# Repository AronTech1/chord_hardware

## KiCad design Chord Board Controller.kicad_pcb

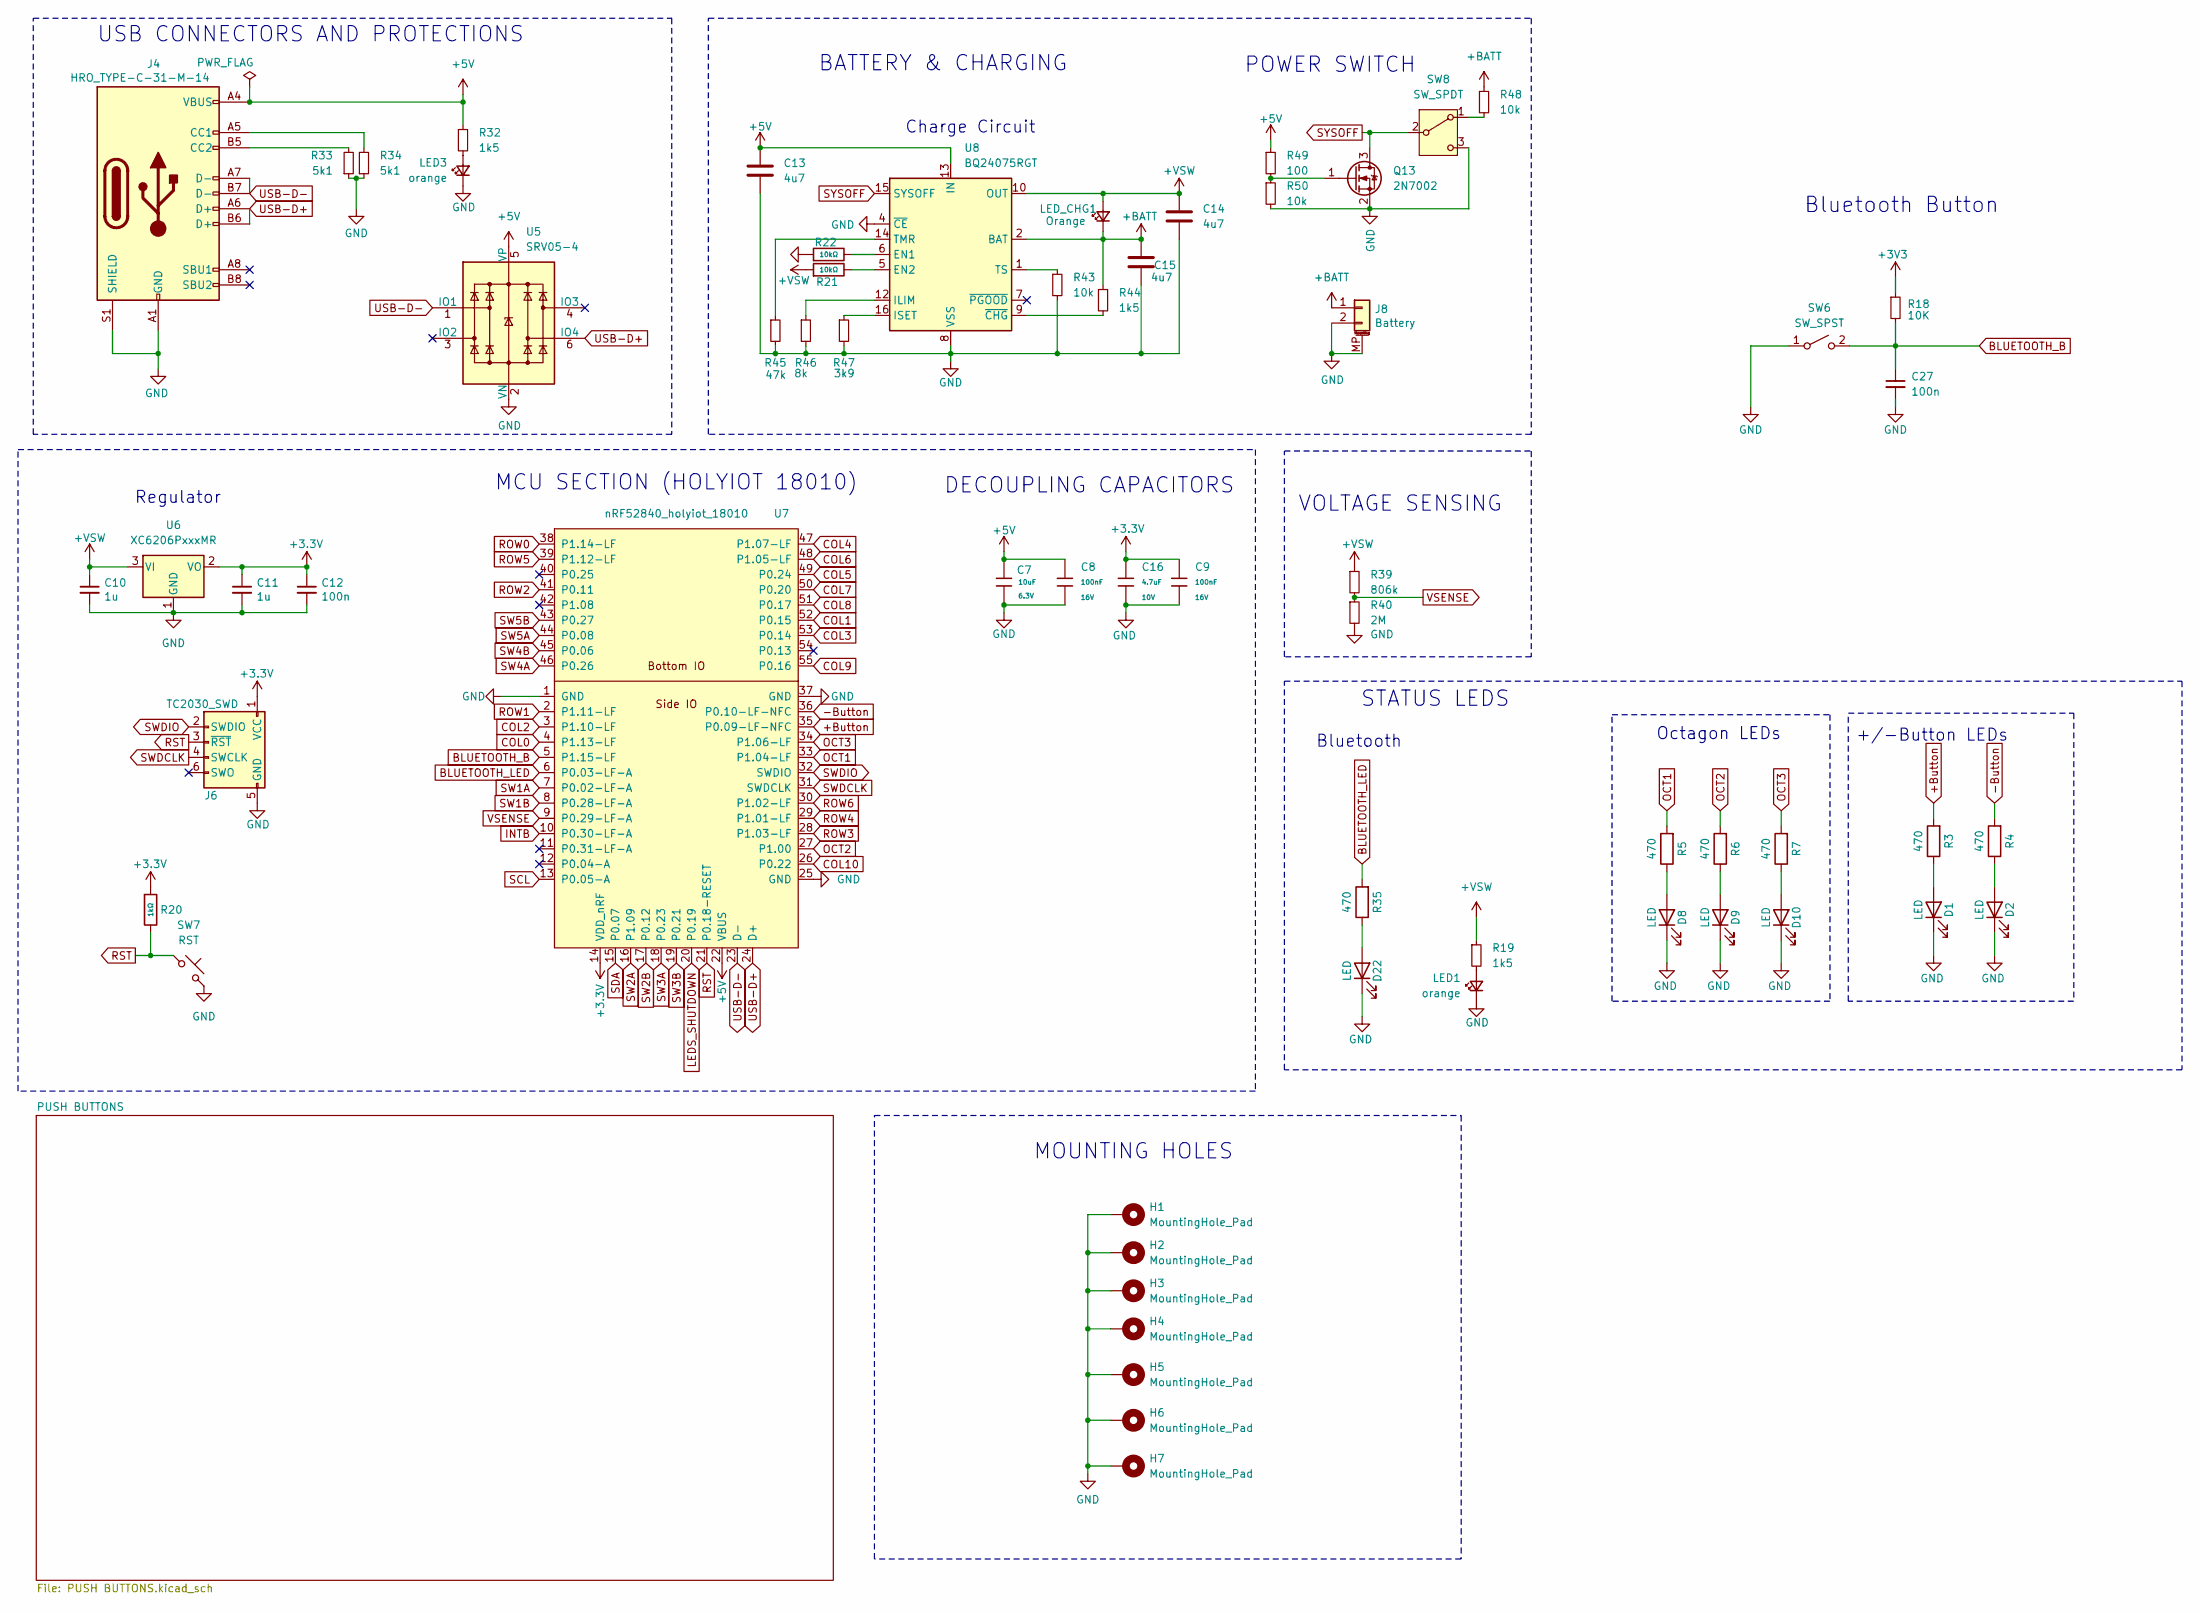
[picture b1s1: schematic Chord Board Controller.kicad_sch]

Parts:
C7: 10uF; C_0402; Voltage Rated 6.3V; Tolerance ±20%; Part CL05A106MQ5NUNC; LCSC C15525
C8, C9: 100nF; C_0402; Voltage Rated 16V; Tolerance ±10%; Part CL05B104KO5NNNC; LCSC C1525
C10, C11: 1u; C_0402_1005Metric; MFR.Part # CL05A105KP5NNNC; JLCPCB part# C14445
C12: 100n; C_0402_1005Metric; MFR.Part # CL05B104KO5NNNC; JLCPCB part# C1525
C13, C14, C15: 4u7; C_0603_1608Metric
C16: 4.7uF; C_0402; Voltage Rated 10V; Tolerance ±20%; Part CL05A475MP5NRNC; LCSC C23733
C27: 100n; C_0402_1005Metric_Pad0.74x0.62mm_HandSolder; Manufacturer Part # GCM155R71H104KE02J; LCSC C2649549
D1, D2, D8, D9, D10: LED; LED_0603_1608Metric
D22: LED; LED_D1.8mm_W1.8mm_H2.4mm_Horizontal_O6.35mm_Z8.2mm
H1, H2, H3, H4, H5, H6, H7: MountingHole_Pad; MountingHole_2.2mm_M2; MFR.Part # DNP; JLCPCB part# DNP
J4: HRO_TYPE-C-31-M-14; USB_C_Receptacle_HRO_TYPE-C-31-M-14; MFR.Part # TYPE-C-31-M-12; JLCPCB part# C165948
J6: TC2030_SWD; CON_TC2030_outlined; MFR.Part # DNP; JLCPCB part# DNP
J8: Battery; JST_PH_S2B-PH-K_1x02_P2.00mm_Horizontal; LCSC C505023
LED1, LED3: orange; LED_D1.8mm_W1.8mm_H2.4mm_Horizontal_O6.35mm_Z8.2mm
LED_CHG1: Orange; LED_D1.8mm_W1.8mm_H2.4mm_Horizontal_O6.35mm_Z8.2mm
Q13: 2N7002; SOT-23
R3, R4, R5, R6, R7: 470; R_0402_1005Metric
R18: 10K; R_0402_1005Metric_Pad0.72x0.64mm_HandSolder; Manufacturer Part # CRCW040210K0FKED; LCSC C71617
R19, R32: 1k5; R_0402_1005Metric; MFR.Part # 0402WGF1501TCE; JLCPCB part# C25867
R20: 1kΩ; R_0402; Overload Voltage (Max) 50V; Tolerance ±1%; Part 0402WGF1001TCE; LCSC C11702
R21, R22: 10kΩ; R_0402; Overload Voltage (Max) 50V; Tolerance ±1%; Part 0402WGF1002TCE; LCSC C25744
R33, R34: 5k1; R_0402_1005Metric; MFR.Part # 0402WGF5101TCE; JLCPCB part# C25905
R35: 470; R_0603
R39: 806k; R_0402_1005Metric; MFR.Part # 0402WGF8063TCE; JLCPCB part# C29263
R40: 2M; R_0402_1005Metric; MFR.Part # 0402WGF2004TCE; JLCPCB part# C11512
R43, R48, R50: 10k; R_0603_1608Metric_Pad0.98x0.95mm_HandSolder
R44: 1k5; R_0603_1608Metric_Pad0.98x0.95mm_HandSolder
R45: 47k; R_0603_1608Metric_Pad0.98x0.95mm_HandSolder
R46: 8k; R_0603_1608Metric_Pad0.98x0.95mm_HandSolder
R47: 3k9; R_0603_1608Metric_Pad0.98x0.95mm_HandSolder
R49: 100; R_0603_1608Metric_Pad0.98x0.95mm_HandSolder
SW6: SW_SPST; SW_Tactile_SPST_Angled_PTS645Vx31-2LFS; Manufacturer Part # DTSA-61K-V; LCSC C483771
SW7: RST; SW_SPST_SKQG_WithStem; MFR.Part # FRC0402F1101TS; JLCPCB part# C2909306
SW8: SW_SPDT; SW_MSK12C02-HB
U5: SRV05-4; SOT-23-6; MFR.Part # SRV05-4-P-T7; JLCPCB part# C179173
U6: XC6206PxxxMR; SOT-23; MFR.Part # XC6202P332MR-G; JLCPCB part# C47374
U7: nRF52840_holyiot_18010
U8: BQ24075RGT; VQFN-16-1EP_3x3mm_P0.5mm_EP1.6x1.6mm

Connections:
+3.3V: C9.1, C11.1, C12.1, C16.1, J6.1 (VCC), R20.1, U6.2 (VO), U7.14 (VDD_nRF)
+3V3: R18.1
+BATT: C15.1, J8.1, LED_CHG1.1 (K), R44.1, R48.1, U8.2 (BAT), U8.3 (BAT)
+Button: R3.2, U7.35 (P0.09-LF-NFC)
-Button: R4.2, U7.36 (P0.10-LF-NFC)
BLUETOOTH_B: C27.1, R18.2, SW6.2 (B), U7.5 (P1.15-LF)
BLUETOOTH_LED: R35.2, U7.6 (P0.03-LF-A)
COL0: U7.4 (P1.13-LF); also elsewhere on the board
COL1: U7.52 (P0.15); also elsewhere on the board
COL2: U7.3 (P1.10-LF); also elsewhere on the board
COL3: U7.53 (P0.14); also elsewhere on the board
COL4: U7.47 (P1.07-LF); also elsewhere on the board
COL5: U7.49 (P0.24); also elsewhere on the board
COL6: U7.48 (P1.05-LF); also elsewhere on the board
COL7: U7.50 (P0.20); also elsewhere on the board
COL8: U7.51 (P0.17); also elsewhere on the board
COL9: U7.55 (P0.16); also elsewhere on the board
COL10: U7.26 (P0.22); also elsewhere on the board
GND: C7.2, C8.2, C9.2, C10.2, C11.2, C12.2, C13.2, C14.2, C15.2, C16.2, C27.2, D1.1 (K), D2.1 (K), D8.1 (K), D9.1 (K), D10.1 (K), D22.1 (K), H1.1, H2.1, H3.1, H4.1, H5.1, H6.1, H7.1, J4.A1 (GND), J4.A12 (GND), J4.B1 (GND), J4.B12 (GND), J4.S1 (SHIELD), J6.5 (GND), J8.2, J8.MP (MountPin), LED1.1 (K), LED3.1 (K), Q13.2 (S), R21.2, R22.1, R33.1, R34.1, R40.2, R43.2, R45.2, R46.2, R47.2, R50.2, SW6.1 (A), SW7.2, SW8.3 (C), U5.2 (VN), U6.1 (GND), U7.1 (GND), U7.25 (GND), U7.37 (GND), U8.4 (~CE), U8.5 (EN2), U8.8 (VSS), U8.17 (VSS); also elsewhere on the board
INTB: U7.10 (P0.30-LF-A); also elsewhere on the board
LEDS_SHUTDOWN: U7.20 (P0.19); also elsewhere on the board
unnamed: D1.2 (A), R3.1
unnamed: D2.2 (A), R4.1
unnamed: D8.2 (A), R5.1
unnamed: D9.2 (A), R6.1
unnamed: D10.2 (A), R7.1
unnamed: D22.2 (A), R35.1
unnamed: J4.A5 (CC1), R34.2
unnamed: J4.B5 (CC2), R33.2
unnamed: LED1.2 (A), R19.2
unnamed: LED3.2 (A), R32.2
unnamed: Q13.1 (G), R49.2, R50.1
unnamed: R48.2, SW8.1 (A)
unnamed: R46.1, U8.12 (ILIM)
unnamed: R47.1, U8.16 (ISET)
unnamed: R45.1, U8.14 (TMR)
unnamed: R43.1, U8.1 (TS)
unnamed: R44.2, U8.9 (~CHG)
OCT1: R5.2, U7.33 (P1.04-LF)
OCT2: R6.2, U7.27 (P1.00)
OCT3: R7.2, U7.34 (P1.06-LF)
ROW0: U7.38 (P1.14-LF); also elsewhere on the board
ROW1: U7.2 (P1.11-LF); also elsewhere on the board
ROW2: U7.41 (P0.11); also elsewhere on the board
ROW3: U7.28 (P1.03-LF); also elsewhere on the board
ROW4: U7.29 (P1.01-LF); also elsewhere on the board
ROW5: U7.39 (P1.12-LF); also elsewhere on the board
ROW6: U7.30 (P1.02-LF); also elsewhere on the board
RST: J6.3 (~RST), R20.2, SW7.1, U7.21 (P0.18-RESET)
SCL: U7.13 (P0.05-A); also elsewhere on the board
SDA: U7.15 (P0.07); also elsewhere on the board
SW1A: U7.7 (P0.02-LF-A); also elsewhere on the board
SW1B: U7.8 (P0.28-LF-A); also elsewhere on the board
SW2A: U7.16 (P1.09); also elsewhere on the board
SW2B: U7.17 (P0.12); also elsewhere on the board
SW3A: U7.18 (P0.23); also elsewhere on the board
SW3B: U7.19 (P0.21); also elsewhere on the board
SW4A: U7.46 (P0.26); also elsewhere on the board
SW4B: U7.45 (P0.06); also elsewhere on the board
SW5A: U7.44 (P0.08); also elsewhere on the board
SW5B: U7.43 (P0.27); also elsewhere on the board
SWDCLK: J6.4 (SWCLK), U7.31 (SWDCLK)
SWDIO: J6.2 (SWDIO), U7.32 (SWDIO)
SYSOFF: Q13.3 (D), SW8.2 (B), U8.15 (SYSOFF)
USB-D+: J4.A6 (D+), J4.B6 (D+), U5.6 (IO4), U7.24 (D+)
USB-D-: J4.A7 (D-), J4.B7 (D-), U5.1 (IO1), U7.23 (D-)
VSENSE: R39.2, R40.1, U7.9 (P0.29-LF-A)

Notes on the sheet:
USB CONNECTORS AND PROTECTIONS
+/-Button LEDs
POWER SWITCH
MOUNTING HOLES
Regulator
Octagon LEDs
MCU SECTION (HOLYIOT 18010)
Bluetooth Button
VOLTAGE SENSING
DECOUPLING CAPACITORS
STATUS LEDS
Bluetooth
Charge Circuit
BATTERY & CHARGING
